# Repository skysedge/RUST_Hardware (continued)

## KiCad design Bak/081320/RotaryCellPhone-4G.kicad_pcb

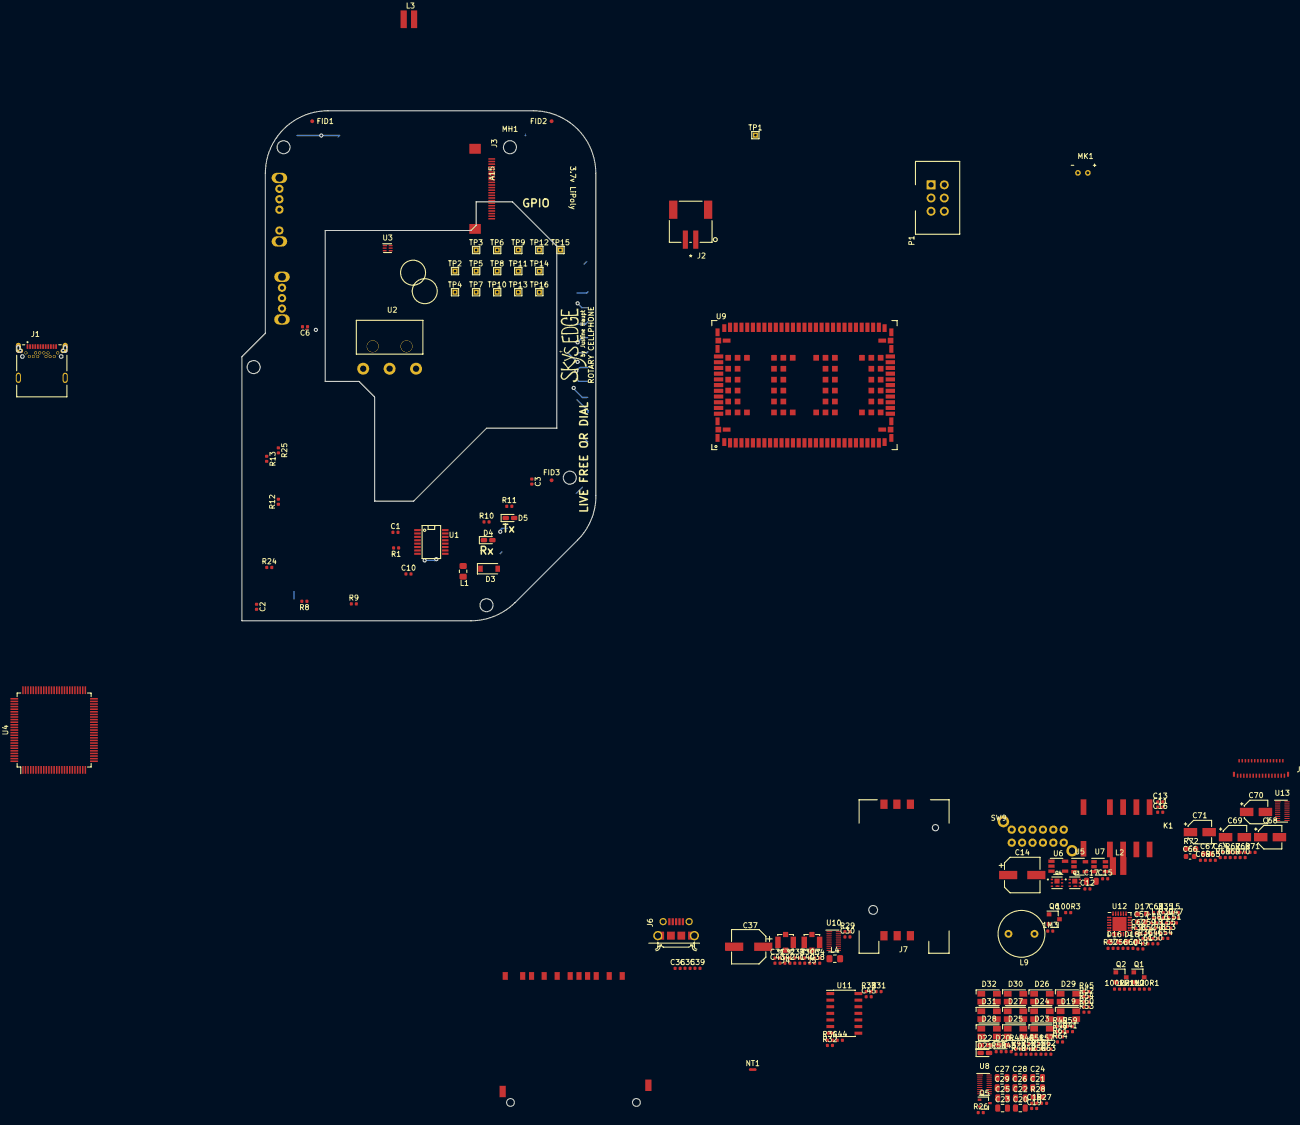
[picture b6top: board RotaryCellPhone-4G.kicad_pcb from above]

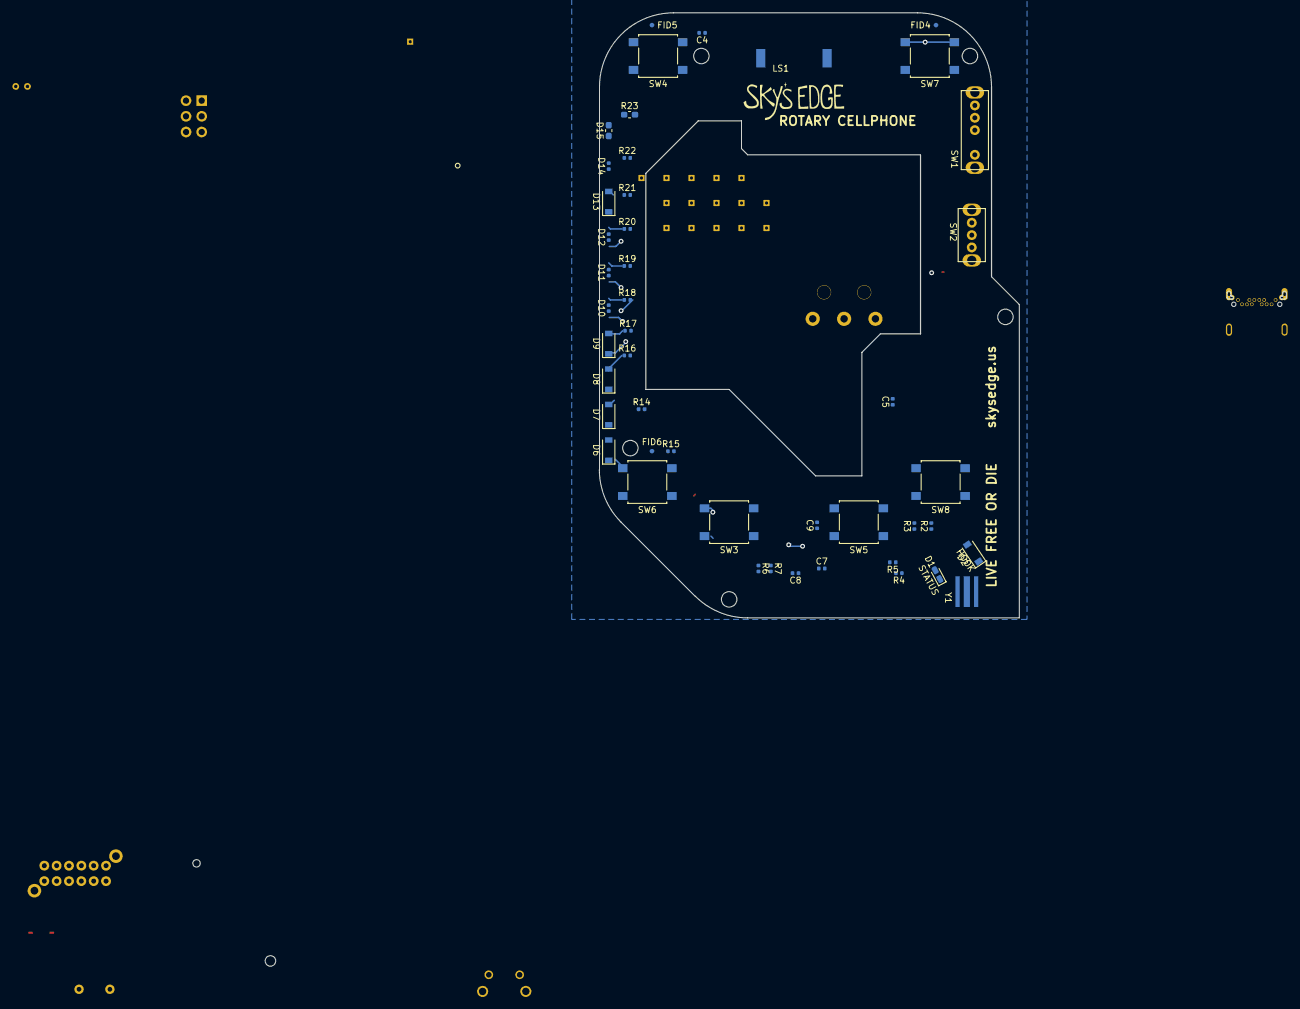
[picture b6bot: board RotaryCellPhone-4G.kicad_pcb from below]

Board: 4 copper layers, 262 parts (47 on the bottom side), 225 nets.

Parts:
1M1, 1M2, 1M3, 100R1, 100R2, 100R3: R_US; R_0402_1005Metric
C1: 22pF; C_0402_1005Metric
C2, C3, C4, C5, C6, C10, C11, C18, C19, C39, C42, C44, C45, C56, C64, C65: .1uF; C_0402_1005Metric
C7, C48, C49, C60, C61: 10nF; C_0402_1005Metric
C8, C9: 47pF; C_0402_1005Metric
C12, C15: 4.7uF; C_0402_1005Metric
C13: 4.7uF or 10uF; C_0402_1005Metric
C14: 100uF, 10V; CP_Elec_6.3x4.5
C16: 1uF/10V; C_0402_1005Metric
C17: 4.7uF/25V; R_0805_2012Metric
C20, C21, C22: 4.7uF/25V; C_0805_2012Metric
C23, C24, C25, C26, C27, C28, C29: 1uF/50V; C_0805_2012Metric
C30: 68pF/50V; C_0402_1005Metric
C31: 15pF/50V; C_0402_1005Metric
C32: 8.2pF/50V; C_0402_1005Metric
C33: 10nF/16V; C_0402_1005Metric
C34: 100nF/16V; C_0402_1005Metric
C35: 330uF/6.3V, TANTALUM 45mR; C_0402_1005Metric
C36, C38, C40, C41: 47pF/50V; R_0402_1005Metric
C37: 100uF; Capacitor_Wurth865080243007
C43: 100nF/16V; R_0402_1005Metric
C46, C47, C62, C63: 27pF; C_0402_1005Metric
C50, C54: 2.2uF; C_0402_1005Metric
C51, C52, C53, C55, C58, C59: 1uF; C_0402_1005Metric
C57: 10uF; C_0603_1608Metric
C66, C67: .1uF/X7R/+-10%; C_0603_1608Metric
C68, C69, C70, C71: 4.7uF/25V; CP_Elec_4x4.5
D1, D20, D21, D22: LED; LED_0603_1608Metric_Castellated
D2, D6: 1N4148; D_SOD-123
D3, D13: D_Schottky; D_SOD-123
D4: RX/GREEN; LED_0603_1608Metric_Castellated
D5: TX/YELLOW; LED_0603_1608Metric_Castellated
D7, D8, D9: MBR0530; D_SOD-123
D10, D11, D12, D14: D_TVS; R_0402_1005Metric
D15, D16, D17, D18: TVS; R_0603_1608Metric_Pad1.05x0.95mm_HandSolder
D19, D23, D24, D25, D26, D27, D28, D29, D30, D31, D32: R/Y; LED_Avago_PLCC4_3.2x2.8mm_CW
FID1, FID2, FID3, FID4, FID5, FID6: Fiducial; Fiducial_0.75mm_Dia_1.5mm_Outer
J1: USB_C_Receptacle; CUI_UJ31-CH-G1-SMT-TR
J2: JST2; S2B-PH-SM4-TBLFSN
J3: FPC; Hirose_FPC_TF31-24S-0.5SH(800)
J4, J5: U.FL; U.FL_Molex_MCRF_73412-0110_Vertical
J6: USB_B_Micro; AMPHENOL_MicroUSB_10118194-0001LF
J7: SIM; SIMHolder_Amph7111S2015X02LF
J8: SDCard; SDCardSocket_Amph_10067847-001RLF
J9: FPC; Hirose_FPC_FH26W-31S-0.3SHW(60)
K1: EE2-3TNU; Relay_Kemet_EE2-3TNU
L1, L4: Ferrite_Bead; R_0805_2012Metric_Pad1.15x1.40mm_HandSolder
L2, L3: 10uH; Inductor_Wurth_74438336100
L5, L6, L7, L8: EMI; L_0402_1005Metric
L9: COIL; Inductor_RLB9012-472KL
LOGO1: Logo1; SkysEdge_21mm
LOGO2: Logo2; SkysEdge_18mm
LS1: Speaker; Speaker_PUI_AR01232MS-SC12-WP-R
MH1, MH2, MH3, MH4, MH5: MountingHole; MountingHole_2.5mm
MK1: 2k2 Electret; Microphone_PUI_POM-2738P-R
NT1: Net-Tie_2; NetTie-2_SMD_Pad0.5mm
P1: ICSP; ICSP_Header
Q1, Q2, Q6: DMG2302UK-7; SOT-23
Q3, Q4: Q_NMOS_POWER; TI_CSD16301Q2
Q5: NMOS; SOT-323_SC-70
R1, R26, R27, R29, R34, R39, R65, R66, R67, R68, R69, R70, R71: 10k; R_0402_1005Metric
R2, R21: 1M; R_0402_1005Metric
R3, R6, R7: 27R; R_0402_1005Metric
R4, R5: 5k1; R_0402_1005Metric
R8, R9, R10, R11: 1k; R_0402_1005Metric
R12: 330R; R_0402_1005Metric
R13, R14, R35, R38: 2k2; R_0402_1005Metric
R15: 6k8; R_0402_1005Metric
R16, R17: 5M1; R_0402_1005Metric
R18: 470R; R_0402_1005Metric
R19, R24, R25, R30, R31, R32, R33: 100k; R_0402_1005Metric
R20: 100; R_0402_1005Metric
R22: 71.5k; R_0402_1005Metric
R23: 10k; R_0603_1608Metric_Pad1.05x0.95mm_HandSolder
R28: 0.47R; R_0603_1608Metric_Pad1.05x0.95mm_HandSolder
R36, R37: 4k7; R_0402_1005Metric
R40, R41, R43, R45, R46, R47, R48, R49, R50, R51, R52, R53, R54, R55, R56, R57, R58, R59, R60, R61, R62, R63, R64: 1k5; R_0402_1005Metric
R42, R44: 27k; R_0402_1005Metric
R72: 620k/+-5%; R_0603_1608Metric_Pad1.05x0.95mm_HandSolder
SW1: SP3T; SP3T_OS103011MA7QP1
SW2: CHARGE RATE SELECT; SPDT_OS102011MA1QN1
SW3, SW4, SW5, SW6, SW7, SW8: Tactile Switch; SW_SPST_B3S-1000
SW9: SW_4P2T; Switch_4PDT_ESwitch-EG4208
TP1, TP2, TP3, TP4, TP5, TP6, TP7, TP8, TP9, TP10, TP11, TP12, TP13, TP14, TP15, TP16: TestPoint_Alt; TestPoint_THTPad_1.0x1.0mm_Drill0.5mm
U1: FT230XS; SSOP-16
U2: ROTARY DIAL ROLLER SWITCH; LimitSwitch_D2F-01FL2-A1
U3: BQ29703DSET; WSON-6_1.5x1.5mm_P0.5mm
U4: ATmega2560V-8AU; TQFP-100_14x14mm_P0.5mm
U5: MCP73831-2-OT; SOT-23-5
U6: AP2112K-3.3; TSOT-23-5
U7: TLV61046A; SOT-23-6
U8, U10, U13: TXB0108DQSR; USON-20_2x4mm_P0.4mm
U9: TOBY-L2; CellModule_TOBY-L2
U11: TXB0104D; SOIC-14_3.9x8.7mm_P1.27mm
U12: MAX9860; WQFN-24-1EP_4x4mm_P0.5mm_EP2.7x2.7mm
Y1: 8MHz; AWSCR-16.00CV-T

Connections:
+3V3: C15.2, C19.1, C20.2, C45.1, C65.1, C66.1, C67.1, J3.15, J3.16, J8.4, J9.12, J9.15, L3.1, R31.1, R32.1, R33.1, R68.1, R69.1, R70.1, R71.1, U6.5, U8.19, U11.1, U13.19
+3V8: C3.1, C4.1, C5.1, C6.1, C16.1, C18.1, C30.1, C31.1, C32.1, C33.1, C34.1, C35.1, C42.1, C44.1, C64.1, K1.4, L2.1, P1.2, R1.2, R24.1, R25.1, U1.12, U4.10, U4.31, U4.61, U4.80, U4.100, U6.1, U7.6, U8.5, U9.70, U9.71, U9.72, U10.19, U11.14, U13.5
+5V: R10.1, R11.1
+12V: C17.1, C68.1, J9.2, J9.6, J9.8, J9.31, L9.1, R21.1, U7.5
/3v3_EN: R19.2, U4.59
/12v_EN: U4.60, U7.4
/AREF: C2.1, U4.98
/AUDIO/BLCK: U9.52, U12.18
/AUDIO/V_INT: C39.1, C56.1, C57.1, C58.1, C59.1, R36.1, R37.1, R39.1, TP7.1, U9.5, U10.1, U10.5, U12.6, U12.11, U12.13
/BELL_PWM: 1M3.1, 100R3.2, U4.1
/CELL TRANSCEIVER/ANT1: J5.1, U9.81
/CELL TRANSCEIVER/ANT2: J4.1, U9.87
/CELL TRANSCEIVER/CTS_1v8: TP13.1, U9.15, U10.3
/CELL TRANSCEIVER/DCD_1v8: TP3.1, U9.12
/CELL TRANSCEIVER/DSR_1v8: TP2.1, U9.10
/CELL TRANSCEIVER/HOST_SELECT0: TP5.1, U9.26
/CELL TRANSCEIVER/HOST_SELECT1: TP6.1, U9.62
/CELL TRANSCEIVER/I2S_GPIO6: U9.61, U12.14
/CELL TRANSCEIVER/I2S_RXD: U9.53, U12.15
/CELL TRANSCEIVER/I2S_SCL: R37.2, U9.54, U12.10
/CELL TRANSCEIVER/I2S_SDA: R36.2, U9.55, U12.9
/CELL TRANSCEIVER/I2S_TXD: U9.51, U12.16
/CELL TRANSCEIVER/I2S_WA: U9.50, U12.17
/CELL TRANSCEIVER/PWR_ON: Q1.3, R30.2, TP10.1, U9.20
/CELL TRANSCEIVER/RESET_N: Q2.3, TP11.1, U9.23
/CELL TRANSCEIVER/RI_1v8: TP1.1, U9.11
/CELL TRANSCEIVER/RTS_1v8: TP12.1, U9.14, U10.2
/CELL TRANSCEIVER/RXD_1v8: TP15.1, U9.17, U10.7
/CELL TRANSCEIVER/TXD_1v8: TP14.1, U9.16, U10.4
/CELL TRANSCEIVER/USB_D+: J6.3, U9.28
/CELL TRANSCEIVER/USB_D-: J6.2, U9.27
/CELL TRANSCEIVER/V_BCKP: C37.1, R30.1, TP16.1, U9.3
/CELL_CTS: U4.94, U10.17
/CELL_ON: 1M1.1, 100R1.2, U4.97
/CELL_PWR_DET: U4.95, U10.20
/CELL_RESET: 1M2.1, 100R2.2, U4.96
/CELL_RTS: U4.93, U10.18
/CELL_RXD: U4.19, U10.15
/CELL_STAT: U4.92, U9.25
/CELL_TXD: U4.18, U10.16
/CHARGING AND POWER MANAGEMENT/+BATT: C13.2, J2.1, K1.5, R12.1, SW9.2, U5.3
/EPD_BUSY: J3.9, U4.71
/EPD_CS: R24.2, U4.75, U8.3
/EPD_DC: U4.74, U8.4
/EPD_RESET: R25.2, U4.72, U8.7
/LED_1A: R45.2, U4.91
/LED_1B: R46.2, U4.90
/LED_2A: R47.2, U4.52
/LED_2B: R48.2, U4.51
/LED_3A: R49.2, U4.17
/LED_3B: R50.2, U4.16
/LED_4A: R51.2, U4.15
/LED_4B: R52.2, U4.13
/LED_5A: R53.2, U4.12
/LED_5B: R54.2, U4.64
/LED_6A: R55.2, U4.63
/LED_6B: R56.2, U4.82
/LED_7A: R57.2, U4.83
/LED_7B: R58.2, U4.84
/LED_8A: R59.2, U4.85
/LED_8B: R60.2, U4.86
/LED_9A: R61.2, U4.87
/LED_9B: R62.2, U4.88
/LED_10A: R63.2, U4.89
/LED_10B: R64.2, U4.42
/LED_HOOK1: R40.2, U4.38
/LED_HOOK2: R41.2, U4.39
/LED_STAT: R44.2, U4.37
/LED_TURNINGOFF: R43.2, U4.36
/LED_TURNINGON: R42.2, U4.35
/MCURX-TO-FTDITX: R8.2, U4.2
/MCUTX-TO-FTDIRX: R9.1, U4.3
/MISO: P1.1, U4.22, U11.10
/MOSI: P1.4, U4.21, U8.2, U11.12, U13.7
/OFFSIGNAL: SW9.8, U4.73
/OLED DRIVER/IREF: J9.7, R72.1
/OLED DRIVER/OLED_A0_3V3: J9.19, R71.2, U13.16
/OLED DRIVER/OLED_CS_3V3: J9.17, R69.2, U13.18
/OLED DRIVER/OLED_RES_3V3: J9.18, R70.2, U13.17
/OLED DRIVER/OLED_SCL_3V3: J9.22, R68.2, U13.20
/OLED DRIVER/OLED_SI_3V3: J9.23, U13.15
/OLED DRIVER/VCOMH: C70.1, J9.4
/OLED DRIVER/VSEGM: C69.1, J9.3
/OLED DRIVER/VSL: C71.1, J9.5
/OLED_AO: U4.24, U13.4
/OLED_CS: U4.78, U13.2
/OLED_XRES: U4.23, U13.3
/RELAY_OFF: D6.1, K1.1, U4.25
/RESET: C1.1, C10.1, P1.5, R1.1, U4.30
/SCK: P1.3, U4.20, U8.1, U11.11, U13.1
/SD CARD/CS_3V3: J8.1, R31.2, U11.2
/SD CARD/DI_3V3: J8.2, U11.3
/SD CARD/DO_3V3: J8.7, U11.5
/SD CARD/SCK_3V3: J8.5, U11.4
/SD_CD: J8.10, U4.77
/SD_CS: U4.76, U11.13
/SW_CLEAR: SW4.1, U4.54
/SW_HOOK: SW7.1, U4.57
/SW_MODE1: SW1.4, U4.44
/SW_MODE2: SW1.3, U4.45
/SW_MODE3: SW1.1, U4.46
/SW_MULTI1: SW3.1, U4.53
/SW_MULTI2: SW6.1, U4.56
/SW_MULTI3: SW5.1, U4.55
/SW_MULTI4: SW8.1, U4.58
/SW_ROTARY: U2.2, U4.70
/ePAPER DRIVER/CS_3v3: J3.12, U8.17
/ePAPER DRIVER/DC_3v3: J3.11, U8.16
/ePAPER DRIVER/GDR: J3.2, Q5.1
/ePAPER DRIVER/MOSI_3v3: J3.14, U8.18
/ePAPER DRIVER/PREVGH: C22.2, D7.1, J3.21
/ePAPER DRIVER/PREVGL: D8.2, J3.23
/ePAPER DRIVER/RESE: J3.3, Q5.2, R28.1
/ePAPER DRIVER/RESET_3v3: J3.10, U8.15
/ePAPER DRIVER/SCK_3v3: J3.13, U8.20
/ePAPER DRIVER/VCOM: C28.1, J3.24
/ePAPER DRIVER/VDD: C29.1, J3.18
/ePAPER DRIVER/VGH: C24.1, J3.5
/ePAPER DRIVER/VGL: C26.1, J3.4
/ePAPER DRIVER/VPP: C25.1, J3.19
/ePAPER DRIVER/VSH: C23.1, J3.20
/ePAPER DRIVER/VSL: C27.1, J3.22
GND: 1M1.2, 1M2.2, 1M3.2, C1.2, C2.2, C3.2, C4.2, C5.2, C6.2, C7.2, C8.2, C9.2, C12.2, C13.1, C14.2, C15.1, C16.2, C17.2, C18.2, C19.2, C20.1, C22.1, C23.2, C24.2, C25.2, C26.2, C27.2, C28.2, C29.2, C30.2, C31.2, C32.2, C33.2, C34.2, C35.2, C36.2, C37.2, C38.2, C39.2, C40.2, C41.2, C42.2, C43.2, C44.2, C45.2, C56.2, C57.2, C58.2, C59.2, C64.2, C65.2, C66.2, C67.2, C68.2, C69.2, C70.2, C71.2, D2.2, D6.2, D9.1, D10.2, D11.2, D12.2, D14.2, D19.2, D19.4, D20.1, D21.1, D22.1, D23.2, D23.4, D24.2, D24.4, D25.2, D25.4, D26.2, D26.4, D27.2, D27.4, D28.2, D28.4, D29.2, D29.4, D30.2, D30.4, D31.2, D31.4, D32.2, D32.4, J1.A1, J1.A12, J1.B1, J1.B12, J1.S1, J3.8, J3.17, J4.2, J5.2, J6.5, J6.6, J7.5, J8.3, J8.6, J8.12, J8.13, J9.10, J9.11, J9.13, J9.14, J9.16, J9.20, J9.21, J9.24, J9.25, J9.26, J9.27, J9.28, J9.29, K1.7, K1.12, NT1.2, P1.6, Q1.2, Q2.2, Q4.4, Q6.2, R4.2, R5.2, R13.1, R14.1, R15.1, R17.1, R22.2, R23.2, R26.2, R27.2, R28.2, R29.2, R34.2, R65.2, R66.2, R67.2, R72.2, SW1.2, SW3.2, SW4.2, SW5.2, SW6.2, SW7.2, SW8.2, SW9.9, TP8.1, U1.5, U1.13, U2.1, U4.11, U4.32, U4.62, U4.81, U4.99, U5.2, U6.2, U7.2, U8.11, U9.2, U9.6, U9.13, U9.30, U9.32, U9.44, U9.46, U9.69, U9.73, U9.74, U9.76, U9.78, U9.79, U9.80, U9.82, U9.83, U9.85, U9.86, U9.88, U9.89, U9.90, U9.92, U9.93, U9.94, U9.95, U9.96, U9.97, U9.98, U9.99, U9.100, U9.101, U9.102, U9.103, U9.104, U9.105, U9.106, U9.107, U9.108, U9.109, U9.110, U9.111, U9.112, U9.113, U9.114, U9.115, U9.116, U9.117, U9.118, U9.119, U9.120, U9.121, U9.122, U9.123, U9.124, U9.125, U9.126, U9.127, U9.128, U9.129, U9.130, U9.131, U9.132, U9.133, U9.134, U9.135, U9.136, U9.137, U9.138, U9.139, U9.140, U9.141, U9.142, U9.143, U9.144, U9.145, U9.146, U9.147, U9.148, U9.149, U9.150, U9.151, U9.152, U10.11, U11.7, U12.12, U13.11, Y1.2
GNDA: C46.2, C47.2, C48.2, C49.2, C50.2, C53.2, C54.2, C55.2, C60.2, C61.2, C62.2, C63.2, D15.2, D16.2, D17.2, D18.2, NT1.1, R35.2, U12.5, U12.24
LL_OE: R23.1, R29.1, R34.1, R65.1, U4.50, U8.6, U10.6, U11.8, U13.6
unnamed: 100R1.1, Q1.1
unnamed: 100R2.1, Q2.1
unnamed: 100R3.1, Q6.1
unnamed: C7.1, D3.1, L1.1
unnamed: C8.1, J1.A7, J1.B7, R7.2
unnamed: C9.1, J1.A6, J1.B6, R6.2
unnamed: C10.2, U1.2
unnamed: C11.1, R12.2, U3.5
unnamed: C11.2, J2.2, Q3.4, R16.2, U3.4
unnamed: C14.1, R20.2, SW9.5
unnamed: C21.1, D8.1, D9.2
unnamed: C21.2, D7.2, L3.2, Q5.3
unnamed: C36.1, D10.1, J7.7, U9.57
unnamed: C38.1, D11.1, J7.3, U9.56
unnamed: C40.1, D12.1, J7.2, U9.58
unnamed: C41.1, C43.1, D14.1, J7.1, U9.59
unnamed: C46.1, D15.1, L5.2, MK1.1
unnamed: C47.1, D16.1, L6.2, MK1.2
unnamed: C48.1, C51.2, L5.1, R35.1
unnamed: C49.1, C52.2, L6.1, R38.1
unnamed: C50.1, R38.2, U12.1
unnamed: C51.1, U12.22
unnamed: C52.1, U12.23
unnamed: C53.1, U12.3
unnamed: C54.1, U12.4
unnamed: C55.1, U12.2
unnamed: C60.1, C62.1, D17.1, L7.1, LS1.1
unnamed: C61.1, C63.1, D18.1, L8.1, LS1.2
unnamed: D1.1, R18.1
unnamed: D2.1, K1.6, SW9.4
unnamed: D3.2, J1.A4, J1.A9, J1.B4, J1.B9
unnamed: D4.1, U1.14
unnamed: D4.2, R10.2
unnamed: D5.1, U1.7
unnamed: D5.2, R11.2
unnamed: D13.1, L4.1
unnamed: D13.2, J6.1
unnamed: D19.1, R40.1
unnamed: D19.3, R41.1
unnamed: D20.2, R42.1
unnamed: D21.2, R43.1
unnamed: D22.2, R44.1
unnamed: D23.1, R45.1
unnamed: D23.3, R46.1
unnamed: D24.1, R47.1
unnamed: D24.3, R48.1
unnamed: D25.1, R49.1
unnamed: D25.3, R50.1
unnamed: D26.1, R51.1
unnamed: D26.3, R52.1
unnamed: D27.1, R53.1
unnamed: D27.3, R54.1
unnamed: D28.1, R55.1
unnamed: D28.3, R56.1
unnamed: D29.1, R57.1
unnamed: D29.3, R58.1
unnamed: D30.1, R59.1
unnamed: D30.3, R60.1
unnamed: D31.1, R61.1
unnamed: D31.3, R62.1
unnamed: D32.1, R63.1
unnamed: D32.3, R64.1
unnamed: J1.A5, R5.1
unnamed: J1.B5, R4.1
unnamed: J8.8, R32.2
unnamed: J8.9, R33.2
unnamed: L2.2, U7.1
unnamed: L7.2, U12.7
unnamed: L8.2, U12.8
unnamed: L9.2, Q6.3
unnamed: Q3.1, Q4.1
unnamed: Q3.2, Q4.2
unnamed: Q3.3, R16.1, U3.3
unnamed: Q3.5, Q4.5
unnamed: Q3.6, Q4.6
unnamed: Q4.3, R17.2, U3.2
unnamed: R2.1, R3.1, Y1.3
unnamed: R2.2, U4.34, Y1.1
unnamed: R3.2, U4.33
unnamed: R6.1, U1.8
unnamed: R7.1, U1.9
unnamed: R8.1, U1.1
unnamed: R9.2, U1.4
unnamed: R13.2, U3.6
unnamed: R14.2, SW2.1
unnamed: R15.2, SW2.3
unnamed: R18.2, U5.1
unnamed: R19.1, U6.3
unnamed: R20.1, SW9.3
unnamed: R21.2, R22.1, U7.3
unnamed: R26.1, U8.8, U8.9, U8.10
unnamed: R27.1, U8.12, U8.13, U8.14
unnamed: R39.2, U12.19
unnamed: R66.1, U13.8, U13.9, U13.10
unnamed: R67.1, U13.12, U13.13, U13.14
unnamed: SW2.2, U5.5
unnamed: TP4.1, U9.49
unnamed: TP9.1, U9.60
unnamed: U1.3, U1.10, U1.11
VBUS: C12.1, D1.2, L1.2, L4.2, U5.4

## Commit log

2024-06-24 initial commit to github
2025-03-03 removed TestBoard from this repo
2025-03-03 renamed project
2025-03-03 changed file names
2025-03-04 updated naming convention
2025-03-04 removed old DB dir
2025-03-04 fixed naming conventions
2025-03-04 changed name of backups folder to old
2025-03-04 fixed part no.s for availability
2025-03-04 made changes
2025-03-04 Added cable clip
    Moved USBD-1 test point and trace slightly.
    Added cable clip
2025-03-04 Moved 1 trace to test Git Pushing.
    No large changes. Move 1 trace ~0.1mm
2025-03-16 for phase 1 prod
